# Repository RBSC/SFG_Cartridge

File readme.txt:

Yamaha SFG 05/01-S Cartridge Board v1.2
Copyright (c) 2017 RBSC

The Setup
---------

After assembling, the cartridge needs to be programmed in order to function properly. The following steps are necessary:

 1. Upload the Altera's firmware
 2. Program the BIOS with the provided ROM file

How to upload the firmware
--------------------------

The below instructions are for programming the Altera chip.

 1. Solder jumper pins both sides of C3 capacitor (only for older boards without power connector)
 2. Prepare the ByteBlaster 2 programmer, open the Quartus II software, keep default JTAG selection
 3. Supply 5v power to the cartridge board via jumper pins (mind the correct polarity!)
 4. Connect the ByteBlaster's cable to the AS socket of the cartridge (make sure you connect the cable correctly!)
 5. Click "Autodetect" in Quartus II software, the Altera chip should be found and ready for programming
 6. Use "Change file" option and select the .POF file from the "Firmware" directory
 7. Enable the checkboxes: "Program/Configure", "Verify" and "Blank Check"
 8. Click "Start" and monitor the programming and verification process

If the programming completed successfully, disconnect the ByteBlaster's cable and 5v power from the board.

You must also write the provided ROM file from BIOS directory into the W27C512 EEPROM chip (PLCC32) using any EEPROM programmer.
The ROM file contains 2 different BIOS versions that can be selected by the special jumper on the board.

Using the extension board
-------------------------

The separate extension board was created for the SFG cartridge in order to make available standard SFG sockets - left and right
RCA audio sockets, music keyboard socked and MIDI IN and MIDI OUT sockets. The board can be either mounted on top of the
cartridge or it can be connected to the cartridge with the standard IDE ribbon cable.

IMPORTANT! When connecting the ribbon cable or plugging the extension board on top of the cartridge please make sure that you are
connecting correctly, otherwise damage may occur to your SFG cartridge!

Starting SFG BIOS
-----------------

To start the built-in SFG BIOS make sure that Basic is loaded and type "_musica" or "call musica" without quotes and press Enter.
The BIOS should start immediately. Depending on whether the jumper is installed or not, either the SFG-01 BIOS or SFG-05 BIOS will
be launched. To exit from BIOS software just reboot your MSX.

Notes
-----

If you are using 74HCT04 chip instead of 74LS04 please make sure you add one additional 47pf capacitor. See the 74HCT04_fix_cart.jpg
image for capacitor mounting instructions. This picture shows the placing of an additional capacitor on the board version 1.0. Later
versions of the board have the dedicated place for this capacitor (C50).

IMPORTANT!
----------

The RBSC provides all the files and information for free, without any liability (see the disclaimer.txt file). The provided information,
software or hardware must not be used for commercial purposes unless permitted by the RBSC. Producing a small amount of bare boards for
personal projects and selling the rest of the batch is allowed without the permission of RBSC.

When the sources of the tools are used to create alternative projects, please always mention the original source and the copyright!

Contact information
-------------------

The members of RBSC group Wierzbowsky, Ptero and DJS3000 can be contacted via the MSX.ORG or ZX-PK.RU forums. Just send a personal
message and state your business.

The RBSC repository can be found here:

https://github.com/rbsc

-= ! MSX FOREVER ! =-

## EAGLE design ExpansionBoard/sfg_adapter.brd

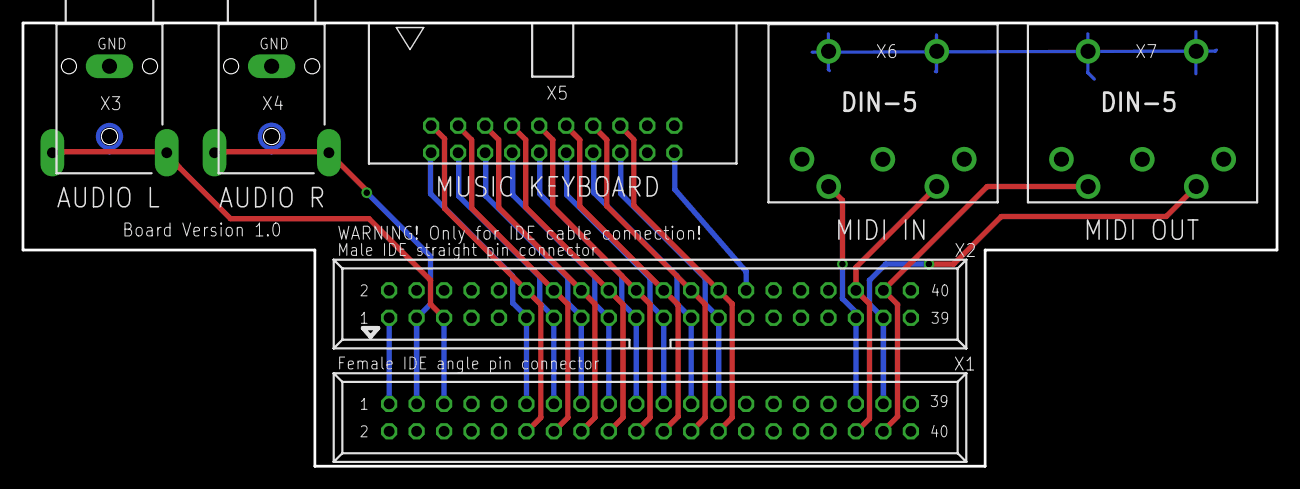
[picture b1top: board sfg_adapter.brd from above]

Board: 2 copper layers, 116.0 x 41.0 mm, 7 parts (0 on the bottom side), 25 nets.

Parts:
X1: SFGSFG; SFG
X2: SFG_CABLESFG_CABLE; SFG_CABLE
X3, X4: RCA
X5: SFG-20
X6, X7: MIDI_CONN_FEMALE_SUPPORT; DIN_5_FEMALE_SUPPORT

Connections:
AUD-L: X1.5, X2.5, X3.AUD
AUD-R: X1.3, X2.3, X4.AUD
GND1: X1.1, X1.2, X1.4, X1.6, X1.7, X1.8, X2.1, X2.2, X2.4, X2.6, X2.7, X2.8, X3.GND, X4.GND
GND7: X1.27, X1.28, X1.29, X1.30, X2.27, X2.28, X2.29, X2.30, X5.17, X5.18, X5.19, X5.20
GND13: X1.33, X1.34, X1.39, X1.40, X2.33, X2.34, X2.39, X2.40, X7.2
RXM+: X1.35, X2.35, X6.4
RXM-: X1.36, X2.36, X6.5
SD0: X1.26, X2.26, X5.16
SD1: X1.25, X2.25, X5.15
SD2: X1.24, X2.24, X5.14
SD3: X1.11, X2.11, X5.1
SD4: X1.23, X2.23, X5.13
SD5: X1.22, X2.22, X5.12
SD6: X1.21, X2.21, X5.11
SD7: X1.12, X2.12, X5.2
ST0: X1.13, X2.13, X5.3
ST1: X1.14, X2.14, X5.4
ST2: X1.15, X2.15, X5.5
ST3: X1.16, X2.16, X5.6
ST4: X1.17, X2.17, X5.7
ST5: X1.18, X2.18, X5.8
ST6: X1.19, X2.19, X5.9
ST7: X1.20, X2.20, X5.10
TXM+: X1.38, X2.38, X7.4
TXM-: X1.37, X2.37, X7.5

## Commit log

2017-03-13 :space_invader: Added .gitattributes & .gitignore files
2017-03-13 Initial commit
    Initial commit
2017-03-15 Expansion board
    Expansion board sources + new pcb of the cartridge
2017-03-16 New board version
    Fixed 3 layout problems
2017-03-28 New board revision
    New board revision + Gerbers
2017-05-07 The sources for v1.0 board and extension board
2017-05-20 Added firmware files
2017-05-21 Firmware readme added
2017-07-10 Board updated to version 1.2
    Board updated to version 1.2
2017-07-12 Gerbers v1.2, updated readme and PCB
2018-07-15 Updated 15.07.2018
    Updated partslist, added schematics files
2018-07-15 Updated 15.07.2018
    Updated schematics
2018-08-07 Updated readme 07.08.2018
    Updated readme 07.08.2018
2020-09-02 Updated 02.09.2020
    Updated the board and schematics. The board now has stop polygons on the
    edge connector. Schematics now has proper values for capacitors. No
    changes in the partslist or functionality were made.
2020-09-02 Merge remote-tracking branch 'origin/master'
    # Conflicts:
    # .gitattributes
2020-09-02 Revert "Merge remote-tracking branch 'origin/master'"
    This reverts commit 73c8f965ff534ed5ca6353c0233dc5e426959b27.
2020-09-02 Updated 02.09.2020
    Fixed schematics (capacitor values), added stop polygons onto the edge
    connector.
2024-04-22 Case and Labels for the cartridge
2025-03-30 Update 30.03.2025
    Published labels and 3D models of the case that were created by Cristiano Gonçalves.

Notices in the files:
parts and their libraries:
SparkFun-Connectors: Licensing: Creative Commons ShareAlike 4.0 International - https://creativecommons.org/licenses/by-sa/4.0
